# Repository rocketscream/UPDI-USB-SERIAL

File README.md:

# UPDI-USB-SERIAL
A dual USB port adapter with built-in UPDI programmer and a dedicated USB-serial interface board.

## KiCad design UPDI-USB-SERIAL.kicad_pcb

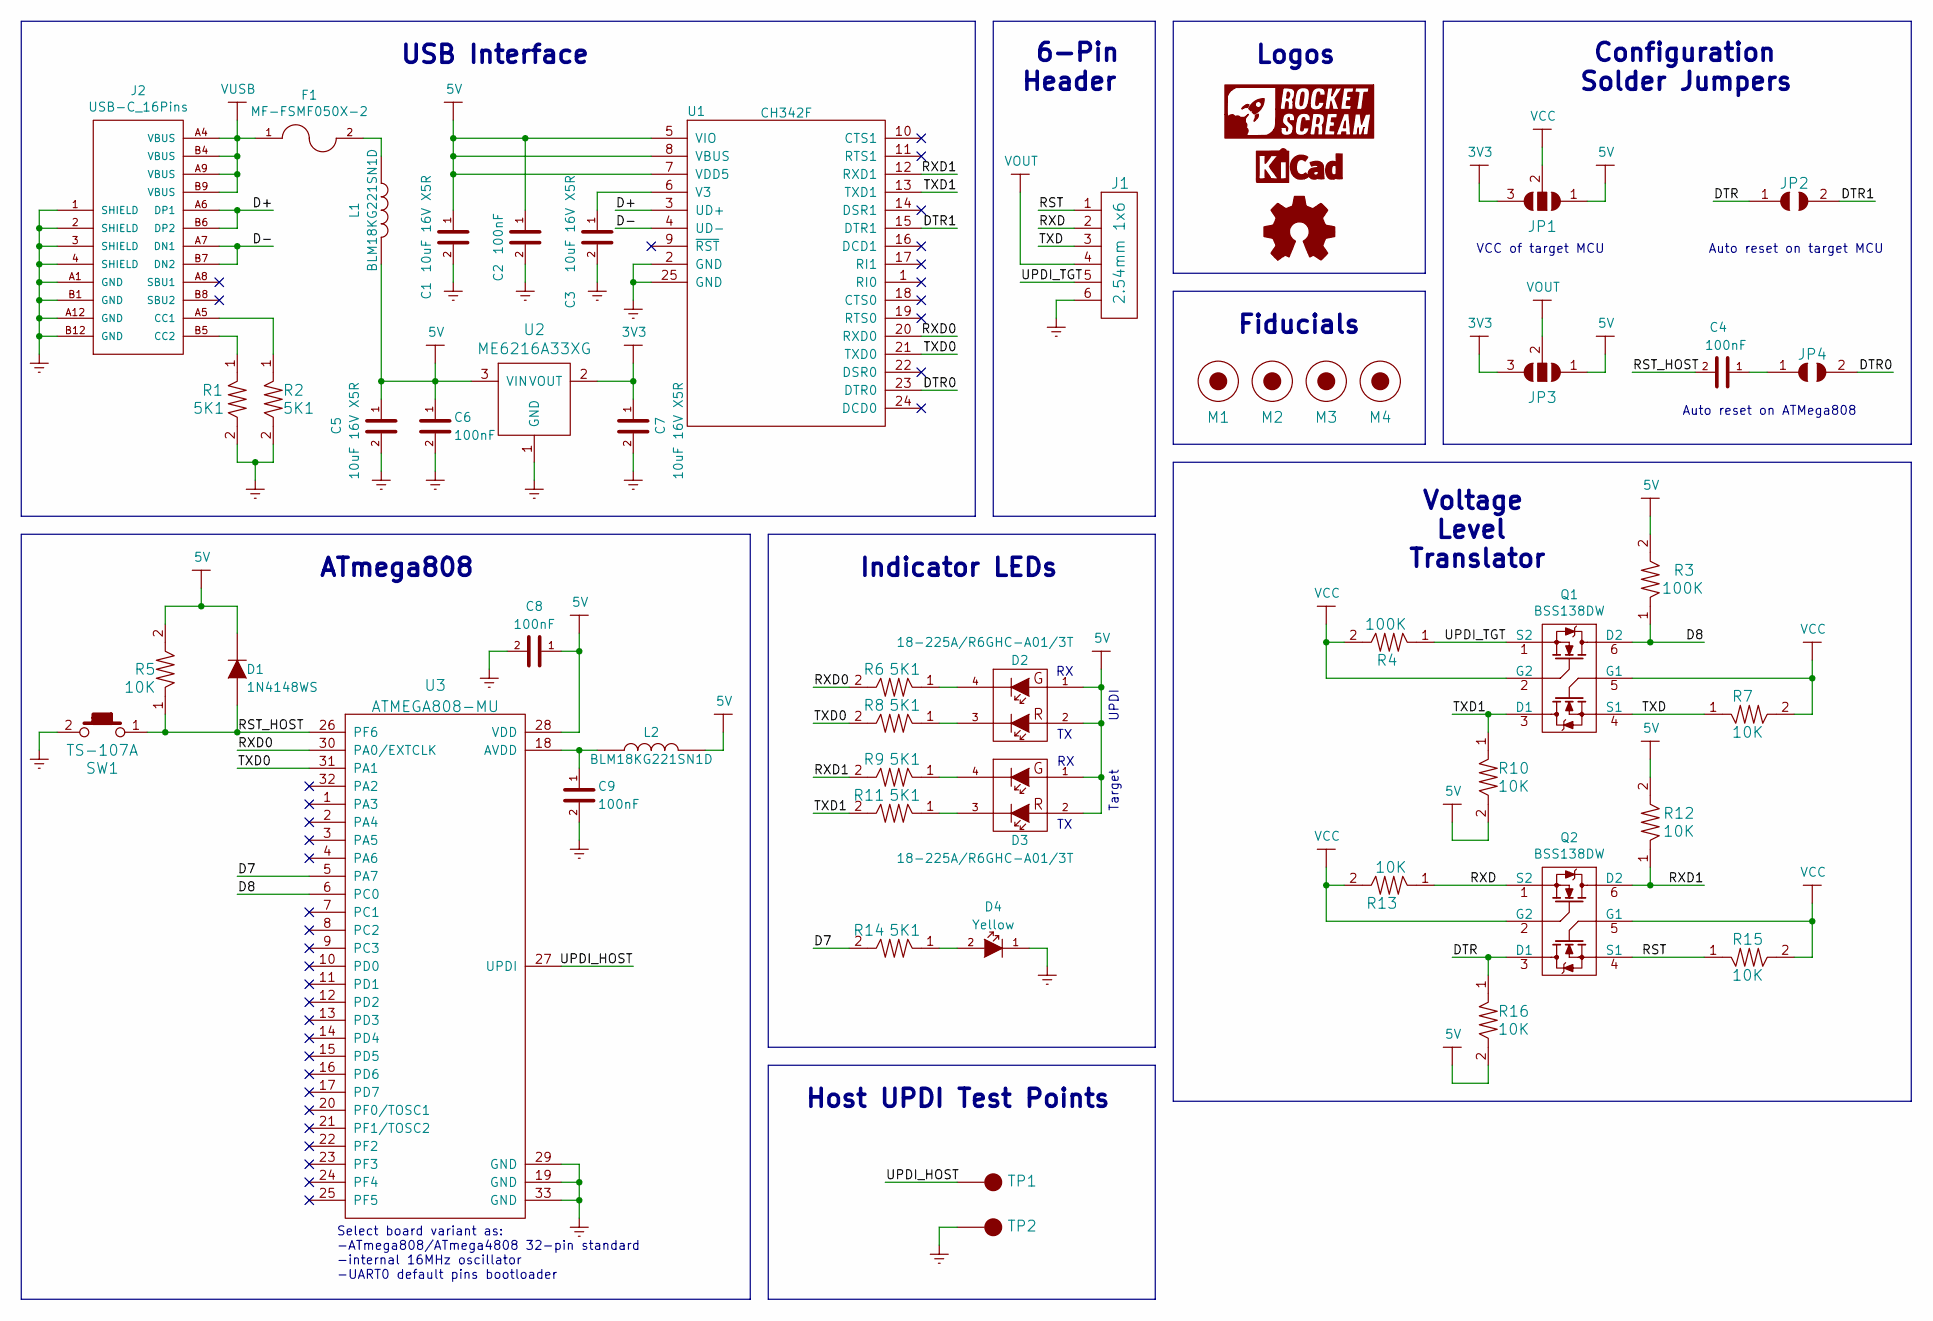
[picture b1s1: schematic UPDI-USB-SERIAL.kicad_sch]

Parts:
C1, C3, C5, C7: 10uF 16V X5R; C_0603
C2, C4, C6, C8, C9: 100nF; C_0603
D1: 1N4148WS; SOD-323
D2, D3: 18-225A/R6GHC-A01/3T; LED-18-225
D4: Yellow; LED_0603
F1: MF-FSMF050X-2; MF-FSMF
J1: 2.54mm 1x6; RCP_1x6_Pitch2.54mm_RightAngle
J2: USB-C_16Pins; TYPE-C16PIN
JP1, JP3: JUMPER-2-WAY; JUMPER-2-WAY-SMD
JP2, JP4: JUMPER-1-WAY; JUMPER-1-WAY-SMD
L1, L2: BLM18KG221SN1D; I_0603
LOGO1: LOGO-ROCKET-SCREAM-HORIZONTAL; LOGO-ROCKET-SCREAM_Horizontal_XSmall
LOGO2: LOGO-OSHW; LOGO-OSHW_XSmall
LOGO3: LOGO-KICAD; LOGO-KICAD_XXXSmall
M1, M2, M3, M4: FIDUCIAL; FIDUCIAL-0.5MM_CROSS
Q1, Q2: BSS138DW; SOT-363_Diodes_Inc
R1, R2, R6, R8, R9, R11, R14: 5K1; R_0603
R3, R4: 100K; R_0603
R5, R7, R10, R12, R13, R15, R16: 10K; R_0603
SW1: TS-107A
TP1, TP2: TEST-PAD; TEST-PAD-1.5MM
U1: CH342F; QFN-24_4x4mm_Pitch0.5mm
U2: ME6216A33XG; SOT-23
U3: ATMEGA808-MU; QFN-32_5x5mm_Pitch0.5mm

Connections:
3V3: C7.1, JP1.3, JP3.3, U2.2 (VOUT)
5V: C1.1, C2.1, C5.1, C6.1, C8.1, D1.1 (K), D2.1 (A), D2.2 (A), D3.1 (A), D3.2 (A), JP1.1, JP3.1, L1.2, L2.2, R3.2, R5.2, R10.2, R12.2, R16.2, U1.5 (VIO), U1.7 (VDD5), U1.8 (VBUS), U2.3 (VIN), U3.28 (VDD)
/D7: R14.2, U3.5 (PA7)
/D8: Q1.6 (D2), R3.1, U3.6 (PC0)
/D+: J2.A6 (DP1), J2.B6 (DP2), U1.3 (UD+)
/D-: J2.A7 (DN1), J2.B7 (DN2), U1.4 (UD-)
/DTR: JP2.1, Q2.3 (D1), R16.1
/DTR0: JP4.2, U1.23 (DTR0)
/DTR1: JP2.2, U1.15 (DTR1)
/RST: J1.1, Q2.4 (S1), R15.1
/RST_HOST: C4.2, D1.2 (A), R5.1, SW1.1, U3.26 (PF6)
/RXD: J1.2, Q2.1 (S2), R13.1
/RXD0: R6.2, U1.20 (RXD0), U3.30 (PA0/EXTCLK)
/RXD1: Q2.6 (D2), R9.2, R12.1, U1.12 (RXD1)
/TXD: J1.3, Q1.4 (S1), R7.1
/TXD0: R8.2, U1.21 (TXD0), U3.31 (PA1)
/TXD1: Q1.3 (D1), R10.1, R11.2, U1.13 (TXD1)
/UPDI_HOST: TP1.1, U3.27 (UPDI)
/UPDI_TGT: J1.5, Q1.1 (S2), R4.1
GND: C1.2, C2.2, C3.2, C5.2, C6.2, C7.2, C8.2, C9.2, D4.1 (K), J1.6, J2.1 (SHIELD), J2.2 (SHIELD), J2.3 (SHIELD), J2.4 (SHIELD), J2.A1 (GND), J2.A12 (GND), J2.B1 (GND), J2.B12 (GND), R1.2, R2.2, SW1.2, TP2.1, U1.2 (GND), U1.25 (GND), U2.1 (GND), U3.19 (GND), U3.29 (GND), U3.33 (GND)
unnamed: C3.1, U1.6 (V3)
unnamed: C4.1, JP4.1
unnamed: C9.1, L2.1, U3.18 (AVDD)
unnamed: D2.3 (K), R8.1
unnamed: D2.4 (K), R6.1
unnamed: D3.3 (K), R11.1
unnamed: D3.4 (K), R9.1
unnamed: D4.2 (A), R14.1
unnamed: F1.2, L1.1
unnamed: J2.A5 (CC1), R2.1
unnamed: J2.B5 (CC2), R1.1
VCC: JP1.2, Q1.2 (G2), Q1.5 (G1), Q2.2 (G2), Q2.5 (G1), R4.2, R7.2, R13.2, R15.2
VOUT: J1.4, JP3.2
VUSB: F1.1, J2.A4 (VBUS), J2.A9 (VBUS), J2.B4 (VBUS), J2.B9 (VBUS)

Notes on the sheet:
6-Pin Header
UPDI
ATmega808
Auto reset on ATMega808
Target
USB Interface
VCC of target MCU
Host UPDI Test Points
Logos
Configuration Solder Jumpers
Indicator LEDs
Auto reset on target MCU
Select board variant as: -ATmega808/ATmega4808 32-pin standard -internal 16MHz oscillator -UART0 default pins bootloader
Voltage Level Translator
Fiducials

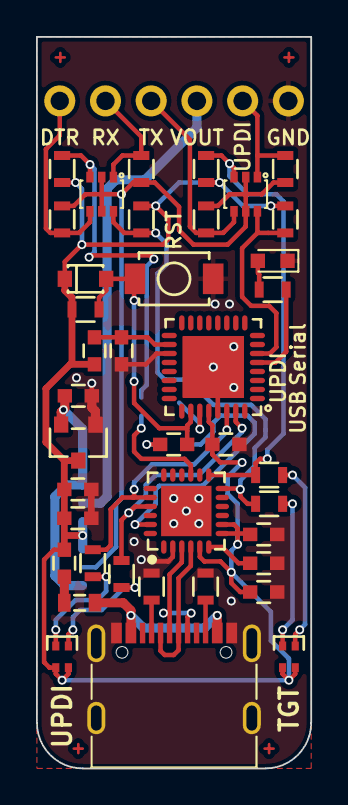
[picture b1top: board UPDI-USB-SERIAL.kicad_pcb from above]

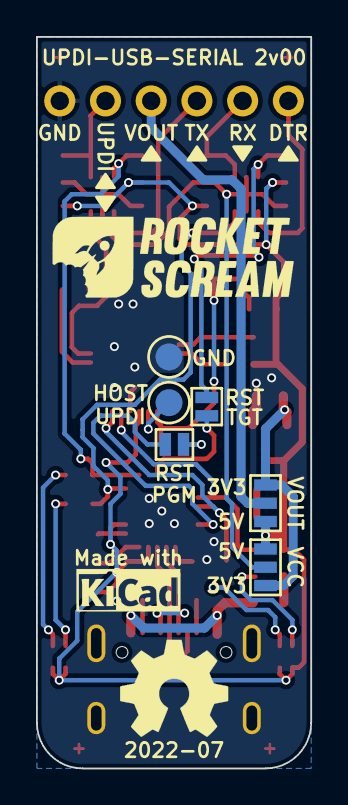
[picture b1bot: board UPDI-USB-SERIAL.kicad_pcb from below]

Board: 2 copper layers, 15.2 x 40.6 mm, 53 parts (9 on the bottom side), 34 nets.

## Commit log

2022-09-25 v1.00
2022-09-25 v2.00
